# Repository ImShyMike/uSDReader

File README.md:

# uSDReader

A simple micro SD to USB A adapter PCB mad eusing KiCAD.

## Render

(some components dont have 3D models because im too lazy to find them)

## Schematic

## PCB

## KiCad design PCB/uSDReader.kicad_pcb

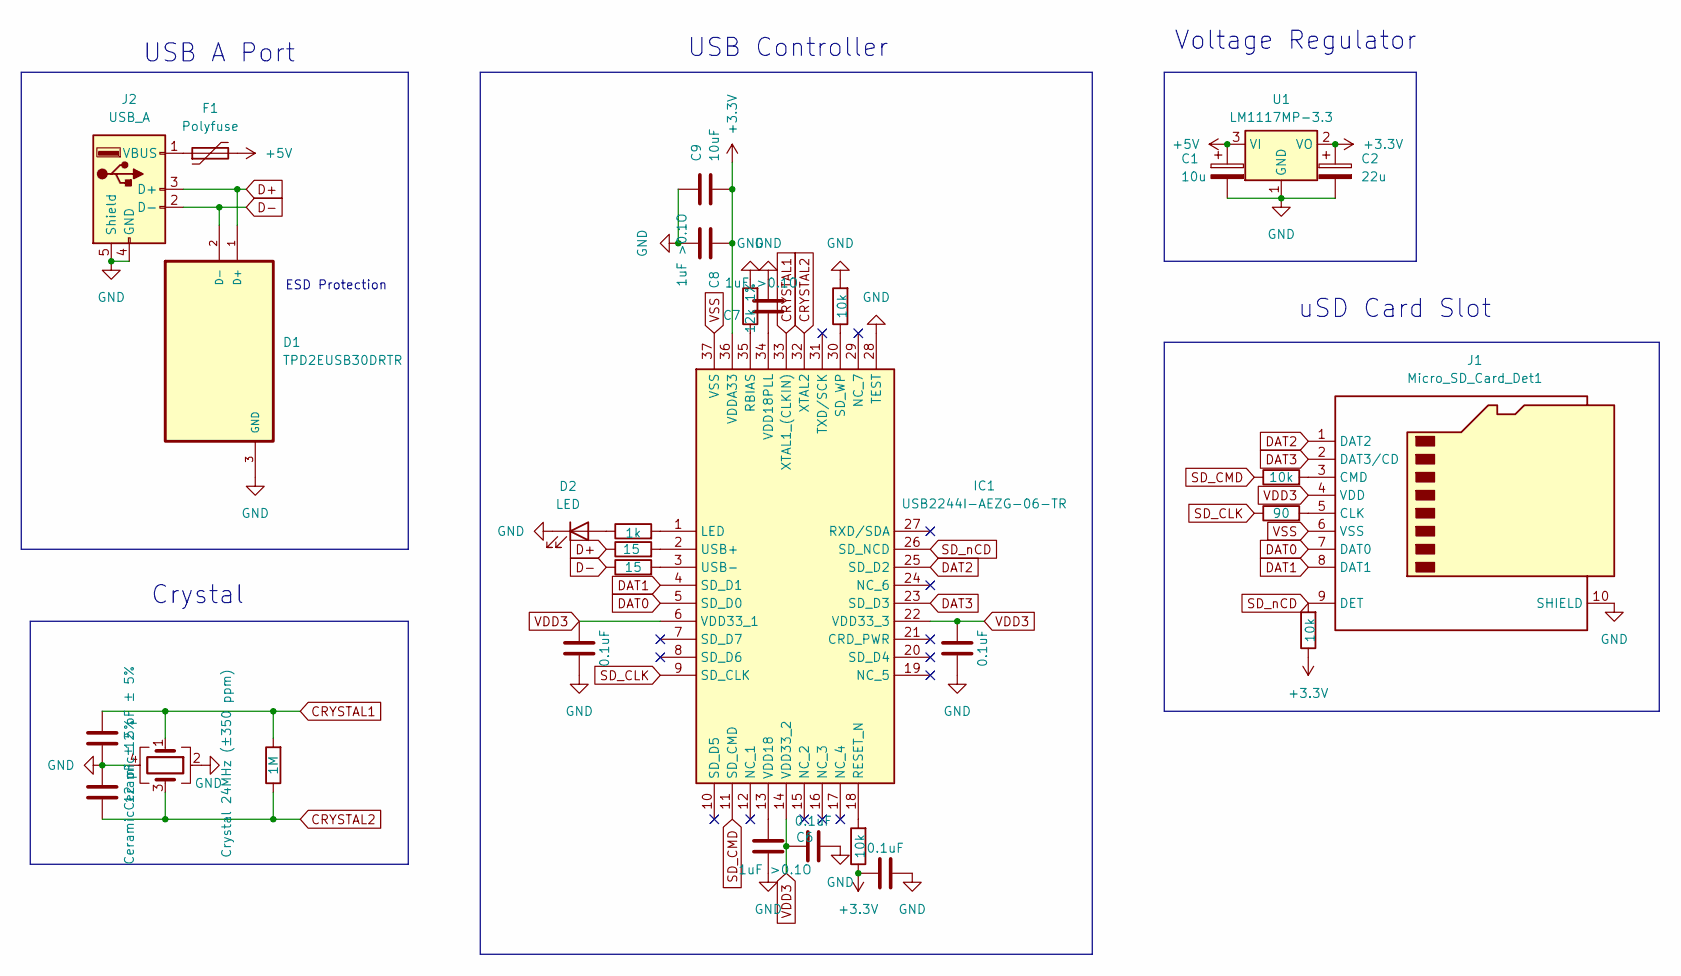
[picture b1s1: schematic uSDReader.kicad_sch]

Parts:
C1: 10u; CP_EIA-1608-08_AVX-J
C2: 22u; CP_EIA-1608-08_AVX-J
C3, C4, C5, C10: 0.1uF; C_0402_1005Metric
C6, C7, C8: 1uF >0.1O; C_0402_1005Metric
C9: 10uF; C_0402_1005Metric
C11, C12: Ceramic 12 pF ± 5%; C_0402_1005Metric
D1: TPD2EUSB30DRTR; SOTFL35P100X50-3N; JLCPCB Part C5182099
D2: LED; LED_0805_2012Metric
F1: Polyfuse; Fuse_0805_2012Metric
IC1: USB2244I-AEZG-06-TR; QFN50P600X600X90-37N-D; Mouser Part Number 579-USB2244IAEZG06TR
J1: Micro_SD_Card_Det1; TF-015; JLCPCB Part C113206
J2: USB_A; USB_A_Receptacle_GCT_USB1046; JLCPCB Part C5393
R1: 1M; R_0603_1608Metric
R2: 90; R_0402_1005Metric
R3, R8, R9, R10: 10k; R_0402_1005Metric
R4, R5: 15; R_0402_1005Metric
R6: 12k 1%; R_0402_1005Metric
R7: 1k; R_0402_1005Metric
U1: LM1117MP-3.3; SOT-223-3_TabPin2
Y2: Crystal 24MHz (±350 ppm); Crystal_SMD_2016-4Pin_2.0x1.6mm; JLCPCB Part C2965580

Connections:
+3.3V: C2.1, C8.1, C9.2, C10.1, IC1.36 (VDDA33), R8.1, R10.1, U1.2 (VO)
+5V: C1.1, F1.2, U1.3 (VI)
CRYSTAL1: C12.2, IC1.33 (XTAL1_(CLKIN)), R1.2, Y2.1
CRYSTAL2: C11.1, IC1.32 (XTAL2), R1.1, Y2.3
D+: D1.1 (D+), J2.3 (D+), R4.1
D-: D1.2 (D-), J2.2 (D-), R5.1
DAT0: IC1.5 (SD_D0), J1.7 (DAT0)
DAT1: IC1.4 (SD_D1), J1.8 (DAT1)
DAT2: IC1.25 (SD_D2), J1.1 (DAT2)
DAT3: IC1.23 (SD_D3), J1.2 (DAT3/CD)
GND: C1.2, C2.2, C3.1, C4.2, C5.2, C6.2, C7.2, C8.2, C9.1, C10.2, C11.2, C12.1, D1.3 (GND), D2.1 (K), IC1.28 (TEST), J1.10 (SHIELD), J2.4 (GND), J2.5 (Shield), R6.2, R9.2, U1.1 (GND), Y2.2, Y2.4
unnamed: D2.2 (A), R7.1
unnamed: IC1.1 (LED), R7.2
unnamed: IC1.35 (RBIAS), R6.1
unnamed: IC1.18 (RESET_N), R8.2
unnamed: IC1.30 (SD_WP), R9.1
unnamed: IC1.2 (USB+), R4.2
unnamed: IC1.3 (USB-), R5.2
unnamed: C6.1, IC1.13 (VDD18)
unnamed: C7.1, IC1.34 (VDD18PLL)
unnamed: J1.5 (CLK), R2.2
unnamed: J1.3 (CMD), R3.2
unnamed: F1.1, J2.1 (VBUS)
SD_CLK: IC1.9 (SD_CLK), R2.1
SD_CMD: IC1.11 (SD_CMD), R3.1
SD_nCD: IC1.26 (SD_NCD), J1.9 (DET), R10.2
VDD3: C3.2, C4.1, C5.1, IC1.6 (VDD33_1), IC1.14 (VDD33_2), IC1.22 (VDD33_3), J1.4 (VDD)
VSS: IC1.37 (VSS), J1.6 (VSS)

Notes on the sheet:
uSD Card Slot
Voltage Regulator
Crystal
USB Controller
USB A Port
ESD Protection

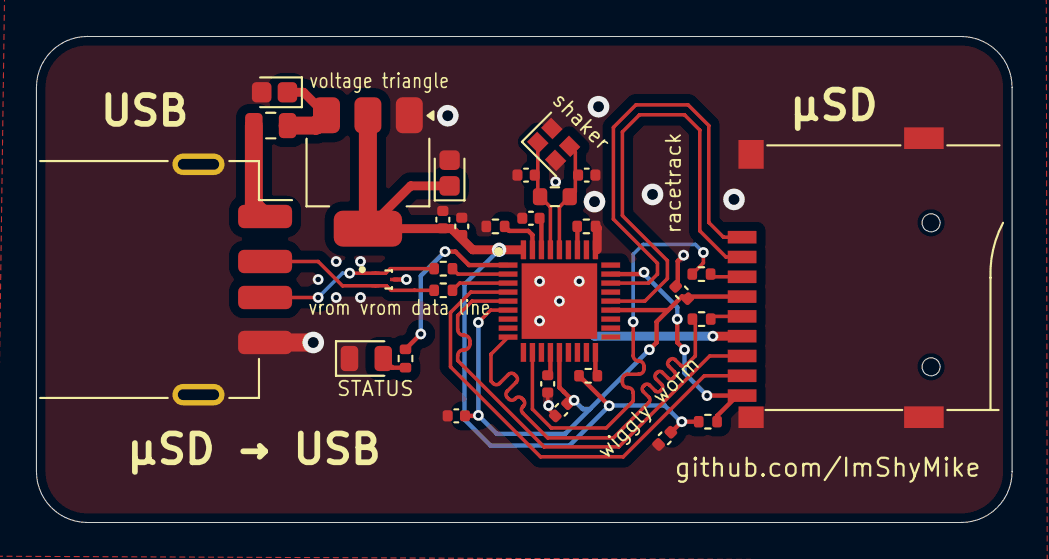
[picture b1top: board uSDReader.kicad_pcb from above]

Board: 2 copper layers, 54.2 x 27.0 mm, 30 parts (0 on the bottom side), 28 nets.

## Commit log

2025-04-21 upload rev3
2025-05-01 REV 4
    Swapped the voltage regulator and the status LED and cleaned up traces
2025-05-21 add production files
